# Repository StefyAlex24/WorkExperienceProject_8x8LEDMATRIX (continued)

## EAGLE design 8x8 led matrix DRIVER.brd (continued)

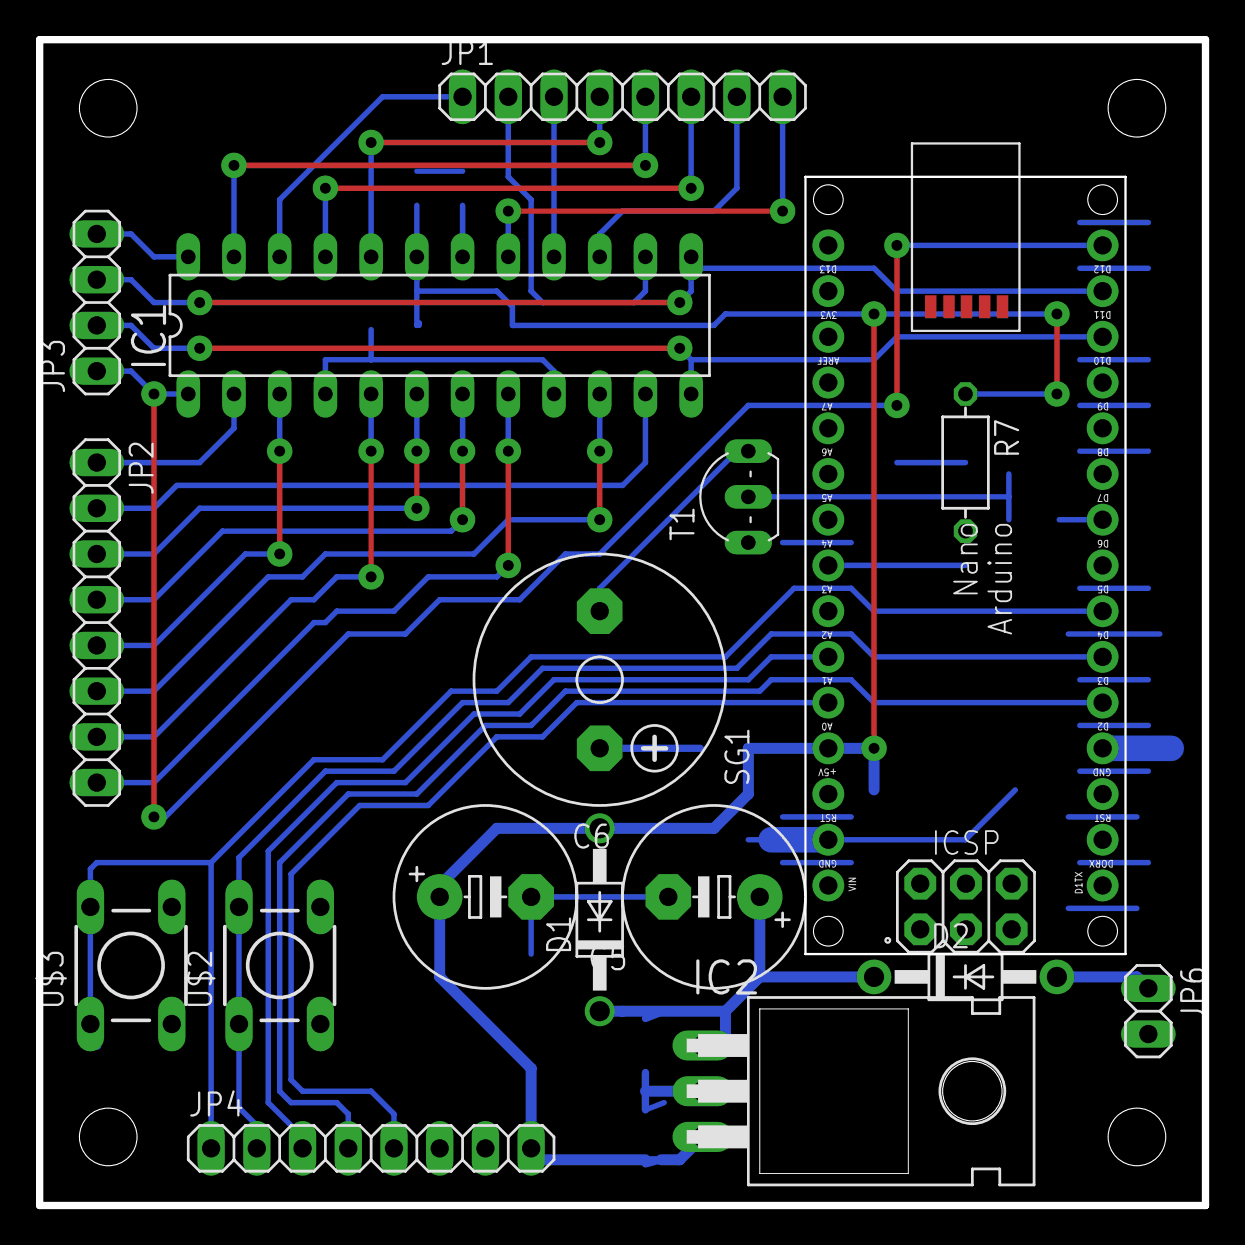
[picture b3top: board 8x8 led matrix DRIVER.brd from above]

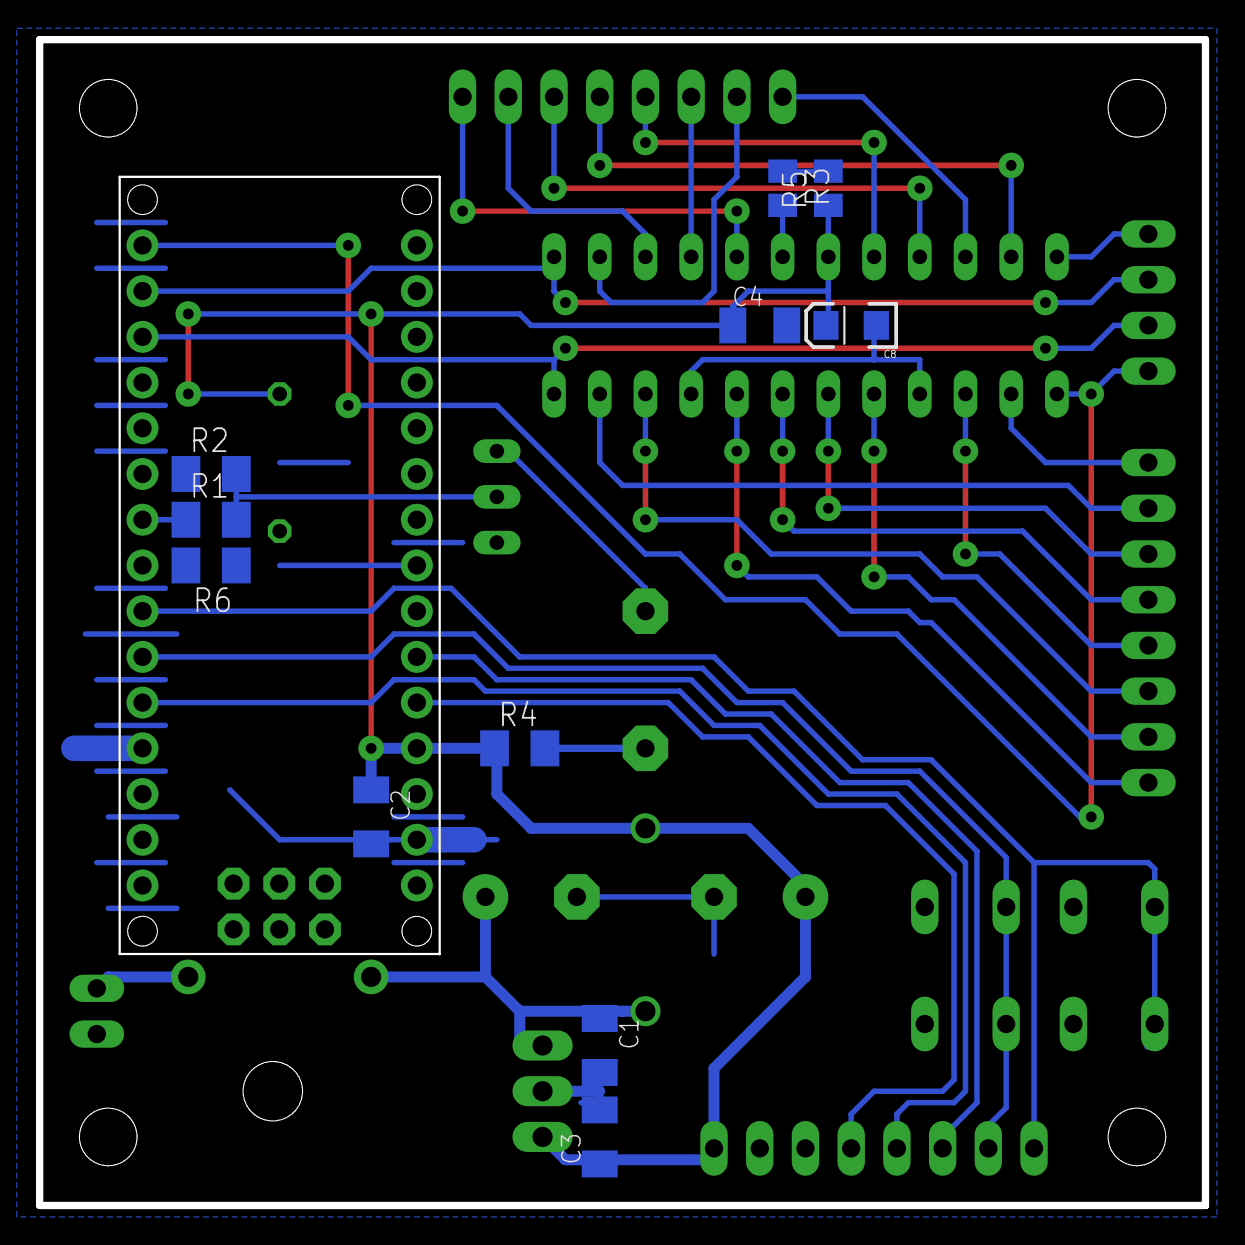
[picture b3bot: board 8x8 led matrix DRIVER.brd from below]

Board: 2 copper layers, 64.8 x 64.8 mm, 28 parts (11 on the bottom side), 36 nets.

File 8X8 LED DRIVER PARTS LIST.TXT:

Partlist

Exported from 8x8 led matrix MAX DRIVER.sch at 16/08/2016 16:16

EAGLE Version 7.5.0 Copyright (c) 1988-2015 CadSoft

Assembly variant: 

Part     Value              Device             Package        Library               Sheet

C1       100N               C-EUC1206K         C1206K         rcl                   1
C2       100N               C-EUC1206K         C1206K         rcl                   1
C3       100N               C-EUC1206K         C1206K         rcl                   1
C4       100N               C-EUC1206K         C1206K         rcl                   1
C5       100U               CPOL-EUE5-10.5     E5-10,5        rcl                   1
C6       100U               CPOL-EUE5-10.5     E5-10,5        rcl                   1
C8       10uF TANT          10UF-TANT          EIA3216        SparkFun-Retired      1
D1       1N4004             1N4004             DO41-10        diode                 1
D2       1N4004             1N4004             DO41-10        adafruit              1
IC1      MAX7219CNG         MAX7219CNG         DIL24-3        maxim                 1
IC2      7805T              7805T              TO220H         adafruit              1
JP1                         PINHD-1X8          1X08           pinhead               1
JP2                         PINHD-1X8          1X08           pinhead               1
JP3                         PINHD-1X4          1X04           pinhead               1
JP4                         PINHD-1X8          1X08           pinhead               1
JP6                         PINHD-1X2          1X02           pinhead               1
PCB1     ARDUINO_NANO       ARDUINO_NANO       ARDUINO_NANO   E14_Arduino_published 1
R1       1K                 R-EU_M1206         M1206          rcl                   1
R2       47K                R-EU_M1206         M1206          rcl                   1
R3       15K                R-EU_M0805         M0805          rcl                   1
R4       200R               R-EU_M1206         M1206          rcl                   1
R5       0R                 R-EU_M0805         M0805          rcl                   1
R6       10K                R-EU_M1206         M1206          rcl                   1
R7       10K THERMISTOR     THERMISTOR-7,5     R-7,5          varistor              1
SG1      F/CM12P            F/CM12P            F/CM12P        buzzer                1
T1       2N2222             2N2222             TO92-EBC-OVAL  adafruit              1
U$2      TACTILE-SWITCH-PTH TACTILE-SWITCH-PTH TAC-SWITCH-PTH GeekAmmo              1
U$3      TACTILE-SWITCH-PTH TACTILE-SWITCH-PTH TAC-SWITCH-PTH GeekAmmo              1

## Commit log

2023-05-09 Add files via upload
    2 layer PCB
2023-05-25 Add files via upload
    Push-button buzzer code to turn on the buzzer at the press of the button. This code makes use of simple PWM using analogWrite() because the buzzer I am using (ABT-414-RC) cannot use DC current hence 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
